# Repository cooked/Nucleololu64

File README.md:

# Nucleololu64
3D printer shield for the STM32 Nucleo 64 board

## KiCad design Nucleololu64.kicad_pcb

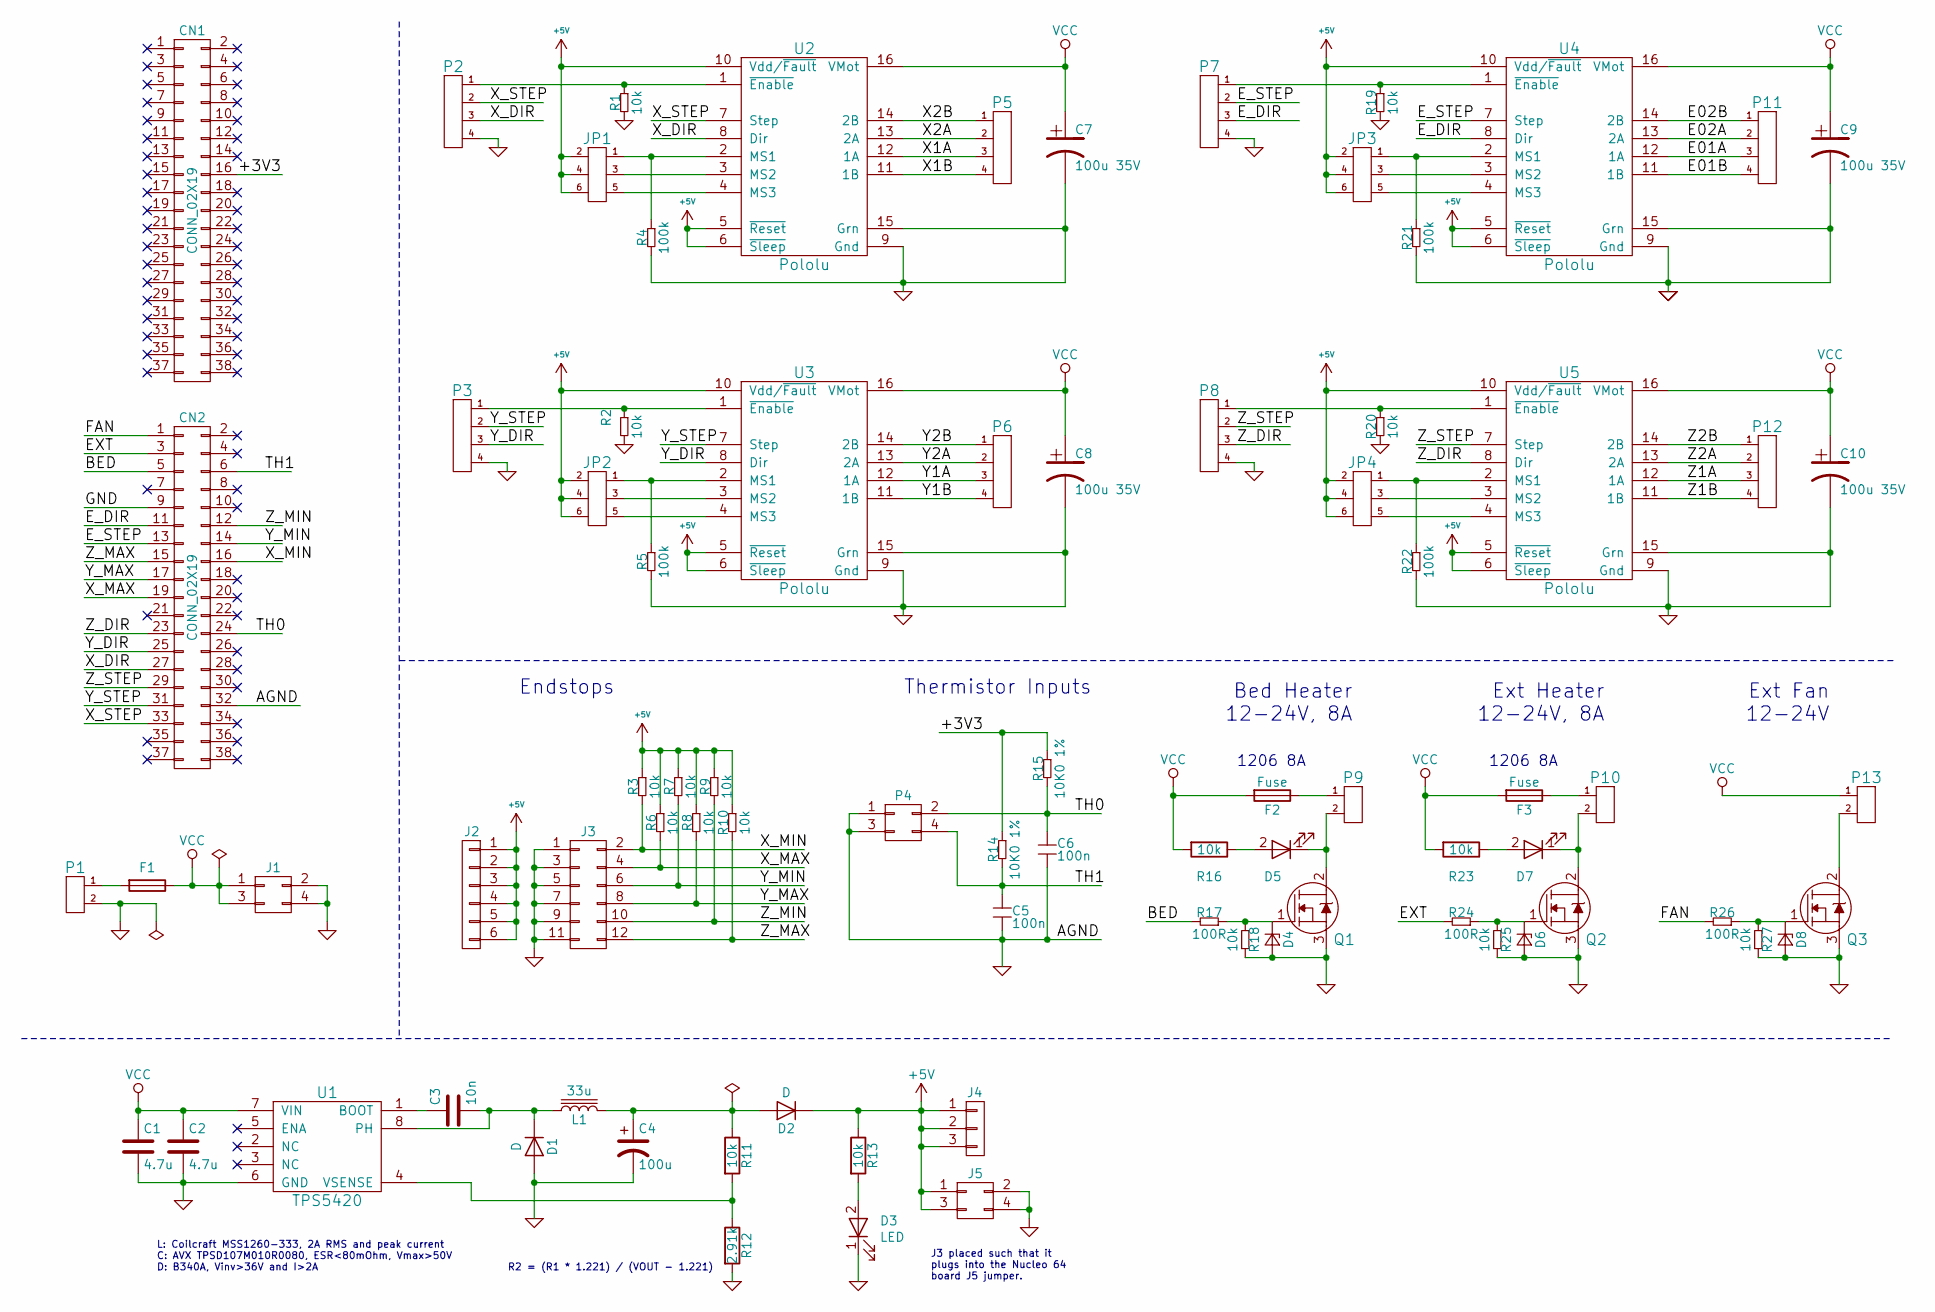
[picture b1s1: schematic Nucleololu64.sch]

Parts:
C1, C2: 4.7u; C_0805_HandSoldering
C3: 10n; C_0805_HandSoldering
C4: 100u; CP_Elec_6.3x7.7
C5, C6: 100n; C_0805_HandSoldering; PartNo GRM188R71C104KA01D
C7, C8, C9, C10: 100u 35V; CP_Elec_6.3x7.7
CN1, CN2: CONN_02X19; Socket_Strip_Straight_2x19_Pitch2.54mm
D1, D2: D; D_SMA_Handsoldering
D3, D5, D7: LED; LED_0603
D4, D6, D8: D_Zener_Small; D_SMA_Handsoldering
F1, F2, F3: Fuse; Fuse_SMD1206_HandSoldering
J1, J5: CONN_02X02; Pin_Header_Straight_2x02_Pitch2.54mm
J2: CONN_01X06; Pin_Header_Straight_1x06_Pitch2.54mm
J3: CONN_02X06; Pin_Header_Straight_2x06_Pitch2.54mm
J4: CONN_01X03; Socket_Strip_Straight_1x03_Pitch2.54mm
JP1, JP2, JP3, JP4: HEADER_3X2; Pin_Header_Straight_2x03_Pitch2.54mm
L1: 33u; L_12x12mm_h6mm
P1: PT_2,5-2-5,0-H; PhoenixContact_MC-G_02x3.50mm_Angled
P2, P3, P7, P8: KK-2.54-4W; Pin_Header_Straight_1x04_Pitch2.54mm; PartNo 22-23-2041
P4: CONN_02X02; Pin_Header_Straight_2x02_Pitch2.54mm
P5, P6, P11, P12: KK-2.54-4W; Molex_KK-6410-04_04x2.54mm_Straight
P9, P10: PT_2,5-2-5,0-H; PhoenixContact_MC-G_02x3.50mm_Angled; PartNo 1935776
P13: PT_1,5-2-3,5-H; PhoenixContact_MC-G_02x3.50mm_Angled; PartNo 1984617
Q1, Q2, Q3: IRLB8743PBF; TO-220-3_Vertical
R1, R3, R6, R7, R8, R10, R11, R13, R16, R19, R20, R23: 10k; R_0805_HandSoldering
R2: 10k; R_0805_HandSoldering; PartNo RMCF0603FT100K
R4, R5, R21, R22: 100k; R_0805_HandSoldering
R9: 10k; R_0805_HandSoldering; PartNo RMCF0603FT10K0
R12: 2.91k; R_0805_HandSoldering
R14, R15: 10K0 1%; R_0805_HandSoldering
R17, R24, R26: 100R; R_0805_HandSoldering; PartNo RMCF0603FT220R
R18, R25, R27: 10k; R_0805_HandSoldering; PartNo RMCF0603FT220R
U1: TPS5420; SOIC-8-N
U2: Pololu; Pololu_socket
U3, U4, U5: Pololu; Pololu_socket; PartNo DRV8825

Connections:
+5V: D2.1 (K), J2.1, J2.2, J2.3, J2.4, J2.5, J2.6, J4.1, J4.2, J4.3, J5.1, J5.3, JP1.2, JP1.4, JP1.6, JP2.2, JP2.4, JP2.6, JP3.2, JP3.4, JP3.6, JP4.2, JP4.4, JP4.6, R3.1, R6.1, R7.1, R8.1, R9.1, R10.1, R13.1, U2.5 (~Reset), U2.6 (~Sleep), U2.10 (Vdd/~Fault), U3.5 (~Reset), U3.6 (~Sleep), U3.10 (Vdd/~Fault), U4.5 (~Reset), U4.6 (~Sleep), U4.10 (Vdd/~Fault), U5.5 (~Reset), U5.6 (~Sleep), U5.10 (Vdd/~Fault); also elsewhere on the board
/+3V3: CN1.16, R14.1, R15.1
/BED: CN2.5, R17.2
/E01A: P11.3, U4.12 (1A)
/E01B: P11.4, U4.11 (1B)
/E02A: P11.2, U4.13 (2A)
/E02B: P11.1, U4.14 (2B)
/EXT: CN2.3, R24.2
/E_DIR: CN2.11, P7.3, U4.8 (Dir)
/E_STEP: CN2.13, P7.2, U4.7 (Step)
/FAN: CN2.1, R26.2
/TH0: C6.1, CN2.24, P4.2, R15.2
/TH1: C5.1, CN2.6, P4.4, R14.2
/X1A: P5.3, U2.12 (1A)
/X1B: P5.4, U2.11 (1B)
/X2A: P5.2, U2.13 (2A)
/X2B: P5.1, U2.14 (2B)
/X_DIR: CN2.27, P2.3, U2.8 (Dir)
/X_MAX: CN2.19, J3.4, R6.2
/X_MIN: CN2.16, J3.2, R3.2
/X_STEP: CN2.33, P2.2, U2.7 (Step)
/Y1A: P6.3, U3.12 (1A)
/Y1B: P6.4, U3.11 (1B)
/Y2A: P6.2, U3.13 (2A)
/Y2B: P6.1, U3.14 (2B)
/Y_DIR: CN2.25, P3.3, U3.8 (Dir)
/Y_MAX: CN2.17, J3.8, R8.2
/Y_MIN: CN2.14, J3.6, R7.2
/Y_STEP: CN2.31, P3.2, U3.7 (Step)
/Z1A: P12.3, U5.12 (1A)
/Z1B: P12.4, U5.11 (1B)
/Z2A: P12.2, U5.13 (2A)
/Z2B: P12.1, U5.14 (2B)
/Z_DIR: CN2.23, P8.3, U5.8 (Dir)
/Z_MAX: CN2.15, J3.12, R10.2
/Z_MIN: CN2.12, J3.10, R9.2
/Z_STEP: CN2.29, P8.2, U5.7 (Step)
GND: C1.2, C2.2, C4.2, C5.2, C6.2, C7.2, C8.2, C9.2, C10.2, CN2.9, CN2.32, D1.2 (A), D3.1 (K), D4.2 (A), D6.2 (A), D8.2 (A), J1.2, J1.4, J3.1, J3.3, J3.5, J3.7, J3.9, J3.11, J5.2, J5.4, P1.2, P2.4, P3.4, P4.1, P4.3, P7.4, P8.4, Q1.3, Q2.3, Q3.3, R1.2, R2.2, R4.2, R5.2, R12.2, R18.1, R19.2, R20.2, R21.2, R22.2, R25.1, R27.1, U1.6 (GND), U2.9 (Gnd), U2.15 (Grn), U3.9 (Gnd), U3.15 (Grn), U4.9 (Gnd), U4.15 (Grn), U5.9 (Gnd), U5.15 (Grn); also elsewhere on the board
unnamed: C3.1, U1.1 (BOOT)
unnamed: C3.2, D1.1 (K), L1.1, U1.8 (PH)
unnamed: C4.1, D2.2 (A), L1.2, R11.1
unnamed: D3.2 (A), R13.2
unnamed: D4.1 (K), Q1.1, R17.1, R18.2
unnamed 43: D5.1 (K), P9.2, Q1.2; also elsewhere on the board
unnamed: D5.2 (A), R16.1
unnamed: D6.1 (K), Q2.1, R24.1, R25.2
unnamed 46: D7.1 (K), P10.2, Q2.2; also elsewhere on the board
unnamed: D7.2 (A), R23.1
unnamed: D8.1 (K), Q3.1, R26.1, R27.2
unnamed 49: F1.2, P1.1; also elsewhere on the board
unnamed 50: F2.1, P9.1; also elsewhere on the board
unnamed 51: F3.1, P10.1; also elsewhere on the board
unnamed: JP1.1, R4.1, U2.2 (MS1)
unnamed: JP1.3, U2.3 (MS2)
unnamed: JP1.5, U2.4 (MS3)
unnamed: JP2.1, R5.1, U3.2 (MS1)
unnamed: JP2.3, U3.3 (MS2)
unnamed: JP2.5, U3.4 (MS3)
unnamed: JP3.1, R21.1, U4.2 (MS1)
unnamed: JP3.3, U4.3 (MS2)
unnamed: JP3.5, U4.4 (MS3)
unnamed: JP4.1, R22.1, U5.2 (MS1)
unnamed: JP4.3, U5.3 (MS2)
unnamed: JP4.5, U5.4 (MS3)
unnamed: P2.1, R1.1, U2.1 (~Enable)
unnamed: P3.1, R2.1, U3.1 (~Enable)
unnamed: P7.1, R19.1, U4.1 (~Enable)
unnamed: P8.1, R20.1, U5.1 (~Enable)
unnamed 68: P13.2, Q3.2; also elsewhere on the board
unnamed: R11.2, R12.1, U1.4 (VSENSE)
VCC: C1.1, C2.1, C7.1, C8.1, C9.1, C10.1, F1.1, F2.2, F3.2, J1.1, J1.3, P13.1, R16.2, R23.2, U1.7 (VIN), U2.16 (VMot), U3.16 (VMot), U4.16 (VMot), U5.16 (VMot); also elsewhere on the board

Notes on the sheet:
Endstops
Thermistor Inputs
Ext Heater 12-24V, 8A
Ext Fan 12-24V
1206 8A
R2 = (R1 * 1.221) / (VOUT - 1.221)
L: Coilcraft MSS1260-333, 2A RMS and peak current C: AVX TPSD107M010R0080, ESR<80mOhm, Vmax>50V D: B340A, Vinv>36V and I>2A
Bed Heater 12-24V, 8A
J3 placed such that it plugs into the Nucleo 64 board J5 jumper.

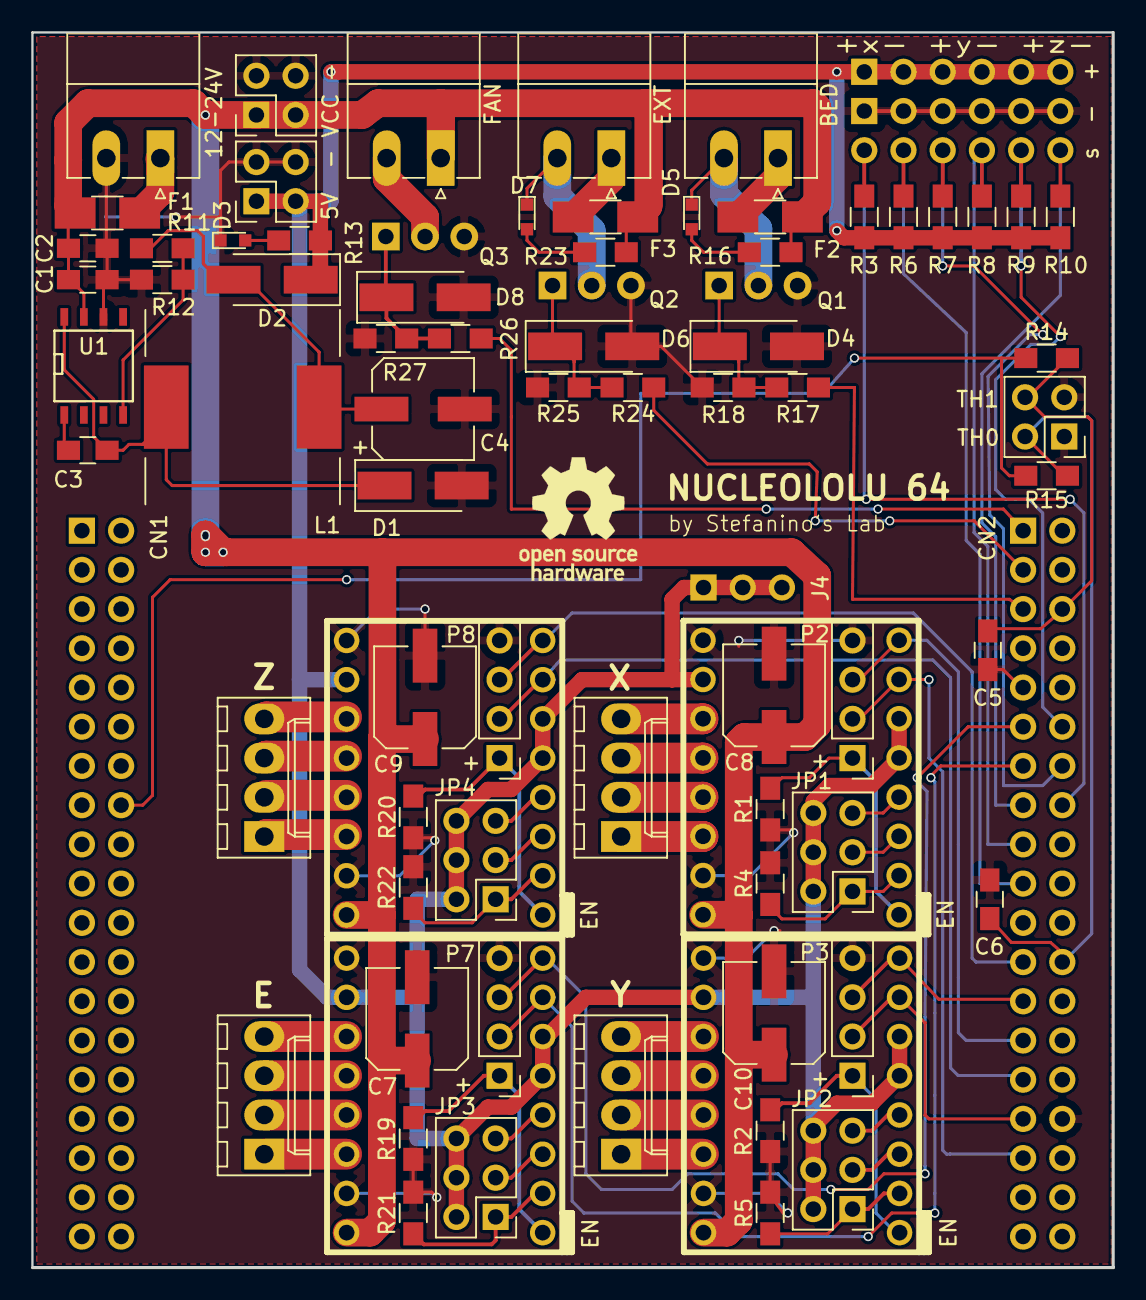
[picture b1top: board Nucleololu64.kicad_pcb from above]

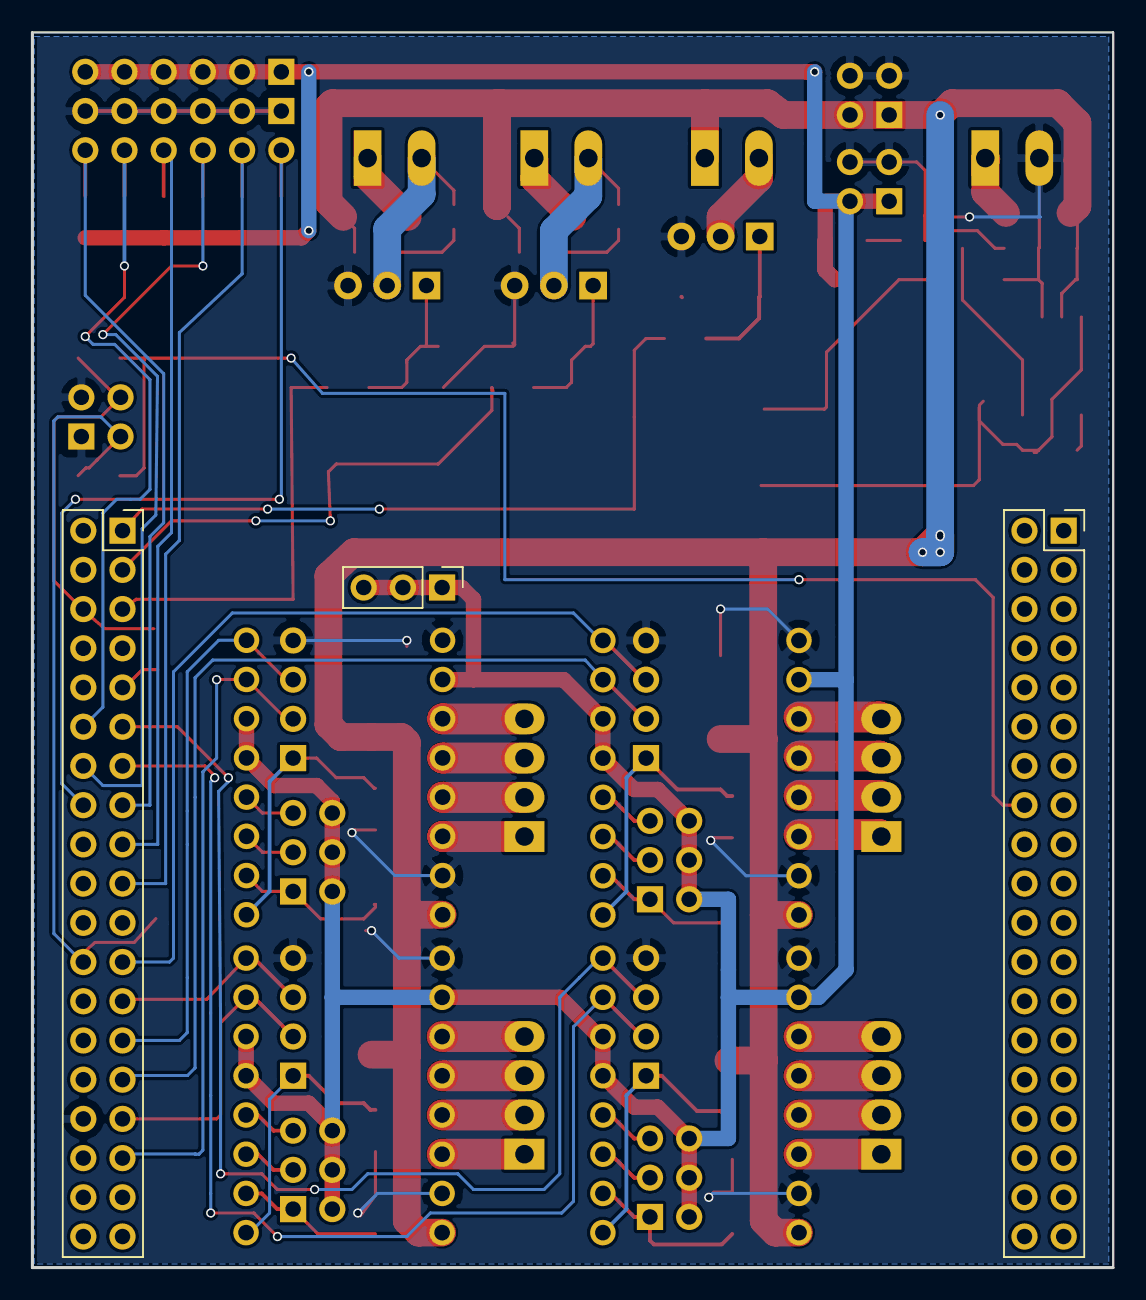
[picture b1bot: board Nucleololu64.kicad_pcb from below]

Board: 2 copper layers, 70.0 x 80.0 mm, 81 parts (4 on the bottom side), 71 nets.

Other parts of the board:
5V  -: CONN_02X02; Pin_Header_Straight_2x02_Pitch2.54mm
12-24V: PT_2,5-2-5,0-H; PhoenixContact_MC-G_02x3.50mm_Angled
BED: PT_2,5-2-5,0-H; PhoenixContact_MC-G_02x3.50mm_Angled
EXT: PT_2,5-2-5,0-H; PhoenixContact_MC-G_02x3.50mm_Angled
FAN: PT_1,5-2-3,5-H; PhoenixContact_MC-G_02x3.50mm_Angled
VCC -: CONN_02X02; Pin_Header_Straight_2x02_Pitch2.54mm

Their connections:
+5V: 5V -.1, 5V -.3; also elsewhere on the board
GND: 5V -.2, 5V -.4, 12-24V.2, VCC -.2, VCC -.4; also elsewhere on the board
unnamed 43: BED.2; also elsewhere on the board
unnamed 46: EXT.2; also elsewhere on the board
unnamed 49: 12-24V.1; also elsewhere on the board
unnamed 50: BED.1; also elsewhere on the board
unnamed 51: EXT.1; also elsewhere on the board
unnamed 68: FAN.2; also elsewhere on the board
VCC: FAN.1, VCC -.1, VCC -.3; also elsewhere on the board

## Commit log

2018-03-10 uploaded schematics
2018-03-10 added datasheets
2018-03-16 batch commit rev.1
2018-03-17 added many manf#
